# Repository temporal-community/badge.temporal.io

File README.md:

# Temporal Replay 2026 Badge

Public source for the Temporal Replay 2026 Badge at `badge.temporal.io`:
firmware, hardware design files, flashing tools, badge apps, release metadata,
and the static documentation site.

This repository is for people who want to flash a badge, build a badge app,
study or modify the firmware, review the hardware package, or contribute fixes
back through GitHub pull requests. Backend services and private event operations
tooling are intentionally not part of this public repo.

## Choose Your Path

| I want to... | Start here |
|---|---|
| Use or reflash a badge | [Get Started](https://badge.temporal.io/get-started), then [`ignition/README.md`](ignition/README.md) |
| Write a MicroPython badge app | [Developer Guide](https://badge.temporal.io/developer-guide), [Apps](https://badge.temporal.io/apps), and [`firmware/initial_filesystem/apps/README.md`](firmware/initial_filesystem/apps/README.md) |
| Change firmware | [`firmware/README.md`](firmware/README.md) and [`firmware/src/README.md`](firmware/src/README.md) |
| Understand flashing and storage | [`ignition/README.md`](ignition/README.md) and [`firmware/docs/STORAGE-MODEL.md`](firmware/docs/STORAGE-MODEL.md) |
| Work with hardware files | [`hardware/README.md`](hardware/README.md) |
| Update public schedule, floor, or speaker data | [`data/README.md`](data/README.md) |
| Update Community Apps metadata | [`registry/README.md`](registry/README.md) |
| Contribute a fix | Open a pull request against `temporal-community/badge.temporal.io`; see [Contributing](#contributing) below. |

## Repository Map

| Path | What It Contains | Start Here |
|---|---|---|
| [`docs/`](docs/) | Static public documentation site for badge users and contributors. | Visit [badge.temporal.io](https://badge.temporal.io/) or open [`docs/index.html`](docs/index.html) locally. |
| [`firmware/`](firmware/) | PlatformIO firmware project for the ESP32-S3 badge, including native C++ screens, MicroPython embedding, OTA, Doom, and the badge filesystem source. | [`firmware/README.md`](firmware/README.md) |
| [`registry/community_apps/`](registry/community_apps/) | Installable MicroPython community app folders that are published in the Community Apps registry but not preloaded into the factory filesystem. | [`registry/README.md`](registry/README.md) |
| [`ignition/`](ignition/) | Temporal-powered build and flashing system built to bulk flash the badge fleet, also useful for one badge. | [`ignition/README.md`](ignition/README.md) |
| [`hardware/`](hardware/) | Public KiCad projects, fabrication outputs, mechanical references, artwork, and board renders from the final hardware package. | [`hardware/README.md`](hardware/README.md) |
| [`data/`](data/) | Public schedule, speaker, and floor data plus the generated bundle embedded by firmware. | [`data/README.md`](data/README.md) |
| [`registry/`](registry/) | Community Apps registry JSON fetched by badges over WiFi. | [`registry/README.md`](registry/README.md) |
| [`release-assets/`](release-assets/) | Notes for OTA and factory image release artifacts. | [`release-assets/README.md`](release-assets/README.md) |
| [`licenses/`](licenses/) | Third-party license texts and notices for bundled non-MIT components. | [`THIRD_PARTY_NOTICES.md`](THIRD_PARTY_NOTICES.md) |
| [`.github/workflows/`](.github/workflows/) | CI release workflow that builds `firmware.bin` and `replay2026-factory-16MB.bin`. | [`.github/workflows/release-firmware.yml`](.github/workflows/release-firmware.yml) |
| [`CONTRIBUTING.md`](CONTRIBUTING.md) | Pull request guidance and change-type checks. | [`CONTRIBUTING.md`](CONTRIBUTING.md) |

## Quick Start

Ignition is the Temporal-powered system we built to bulk flash the Replay 2026
badge fleet. It runs locally and is the default flashing path for one badge or
a connected batch of badges:

```bash
cd ignition
./setup.sh
./doctor.sh
./start.sh -e replay2026 --firmware-dir ../firmware
```

To preload WiFi during an Ignition build, pass credentials on the command line
or create an ignored `firmware/wifi.local.env` from
[`firmware/wifi.local.env.example`](firmware/wifi.local.env.example):

```bash
./start.sh -e replay2026 --firmware-dir ../firmware \
  --wifi-ssid "YourNetwork" --wifi-pass "YourPassword"
```

Developers who want the lower-level path can use PlatformIO directly:

```bash
cd firmware
pio run -e replay2026
pio run -e replay2026 -t upload
pio run -e replay2026 -t uploadfs
```

For a prebuilt release, download `replay2026-factory-16MB.bin` from
[GitHub Releases](https://github.com/temporal-community/badge.temporal.io/releases).
A factory flash restores firmware and filesystem contents and wipes existing
on-badge data; see [`release-assets/README.md`](release-assets/README.md) for
release artifact context. Flash downloaded factory images with Ignition:

```bash
cd ignition
./start.sh --no-build --factory-image ~/Downloads/replay2026-factory-16MB.bin
```

## Firmware Releases

Public releases include two firmware artifacts:

- `firmware.bin`: application image consumed by badge OTA.
- `replay2026-factory-16MB.bin`: complete factory image with bootloader,
  partition table, firmware, FAT filesystem, and bundled shareware Doom data.

The badge OTA updater checks GitHub Releases in
`temporal-community/badge.temporal.io` for `firmware.bin`.

## Licensing

Temporal-authored source, docs, firmware glue, website content, and hardware
files use the MIT License unless a file or notice says otherwise.

Firmware builds that include Doom also include DoomGeneric engine code and the
bundled `doom1.wad` shareware game data. Those components have separate terms;
see [`THIRD_PARTY_NOTICES.md`](THIRD_PARTY_NOTICES.md) and [`licenses/`](licenses/).

## Generated Artifacts

Some generated files are committed because the firmware or public release flow
consumes them directly:

| Path | Source of truth | Commit? |
|---|---|---|
| `data/out/bundle.bin` and `data/out/*.json` | `data/in/` via `data/build-data.py` | Yes |
| `firmware/data/` | `firmware/initial_filesystem/` via `firmware/scripts/generate_startup_files.py` | No, it is a local build mirror |
| `registry/community_apps.json` | `registry/community_apps/` plus curated registry assets via `firmware/scripts/generate_startup_files.py` | Yes |
| `firmware/.pio/`, `ignition/.venv/`, local logs, and WiFi files | Local machine state | No |
| `firmware.bin` and `replay2026-factory-16MB.bin` | GitHub release workflow | Release assets only |

## Contributing

Pull requests are welcome. Good public contributions include docs fixes,
MicroPython examples, badge apps, firmware fixes, Ignition improvements,
hardware documentation corrections, data updates, and registry updates.
See [`CONTRIBUTING.md`](CONTRIBUTING.md) for change-type checklists.

Before opening a PR:

- Keep changes focused and explain what you tested.
- Link related docs when you add or change a workflow.
- Do not commit credentials, local WiFi settings, virtualenvs, PlatformIO build
  output, caches, or private event operations context.
- For firmware changes, include the relevant PlatformIO build or flash command
  you ran.
- For docs-only changes, check that links resolve from the repo root and the
  static docs site still opens from `docs/index.html`.

Use GitHub issues or PR discussion for questions, bug reports, and proposed
app or documentation changes.

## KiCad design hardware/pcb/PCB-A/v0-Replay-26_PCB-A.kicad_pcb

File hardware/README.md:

# Replay 2026 Badge Hardware

This directory contains the public hardware design package for the Replay 2026
Badge. It includes KiCad source projects, manufacturing outputs, mechanical
reference files, and exported artwork/renders for the two-board badge assembly.

This package is based on the final released hardware files from 2026-05-14.
Editor state, macOS metadata, KiCad lock files, local history folders, embedded
`.git` folders, and generated caches were intentionally left out.

## Directory Map

```text
hardware/
|-- pcb/
|   |-- PCB-A/            # Main badge KiCad project
|   |-- PCB-B/            # Backplate KiCad project
|   `-- assets/           # Board outlines, dimensional DXF/SVG, support STEP
|-- fab/
|   |-- PCB-A/            # Main-board fabrication and assembly outputs
|   `-- PCB-B/            # Backplate fabrication outputs
|-- cad/                  # Thumbstick mechanical STEP references
`-- assets/               # Badge artwork, renders, and exported board views
```

## Board Projects

`pcb/PCB-A/` is the main electronics board. Open
`pcb/PCB-A/v0-Replay-26_PCB-A.kicad_pro` in KiCad to inspect or modify the
main badge PCB.

Important files:

- `v0-Replay-26_PCB-A.kicad_sch`: schematic.
- `v0-Replay-26_PCB-A.kicad_pcb`: PCB layout.
- `Temporal.kicad_sym`: project symbol library.
- `Temporal.pretty/`: project footprint library.
- `fp-lib-table` and `sym-lib-table`: KiCad library table entries.

`pcb/PCB-B/` is the backplate/art board. Open
`pcb/PCB-B/pcb-backplate.kicad_pro` in KiCad to inspect or modify it.

Important files:

- `pcb-backplate.kicad_sch`: schematic.
- `pcb-backplate.kicad_pcb`: PCB layout.
- `pcb-backplate.step`: exported mechanical model.

## Fabrication Outputs

The `fab/` directory contains production-facing outputs. Review these files
before ordering boards, especially if the KiCad source has changed.

### PCB-A: Main Board

`fab/PCB-A/` includes:

- [`fab/PCB-A/V0-Replay-26_PCB-A_GBR_260331-R3.zip`](fab/PCB-A/V0-Replay-26_PCB-A_GBR_260331-R3.zip): main-board Gerber package.
- [`fab/PCB-A/V0-Replay-26_PCB-A_BOM-260331-R1.csv`](fab/PCB-A/V0-Replay-26_PCB-A_BOM-260331-R1.csv): bill of materials.
- [`fab/PCB-A/V0-Replay-26_PCB-A_CPL-260331-R1.csv`](fab/PCB-A/V0-Replay-26_PCB-A_CPL-260331-R1.csv): component placement list.
- [`fab/PCB-A/JLCPCB/V0-Replay-26_PCB-A_BOM-260331-R2.csv`](fab/PCB-A/JLCPCB/V0-Replay-26_PCB-A_BOM-260331-R2.csv): JLCPCB-oriented BOM.
- [`fab/PCB-A/JLCPCB/V0-Replay-26_PCB-A_CPL-260331-R2.csv`](fab/PCB-A/JLCPCB/V0-Replay-26_PCB-A_CPL-260331-R2.csv): JLCPCB-oriented placement.
- [`fab/PCB-A/Elecrow_PCBA_Quote_Temporal-PCB-A_260331-R0.xlsx`](fab/PCB-A/Elecrow_PCBA_Quote_Temporal-PCB-A_260331-R0.xlsx): reviewed public-safe supplier quote context.

The imported production note records the `GBR-R2` change as an increased via
diameter to 0.3 mm plus silkscreen for the SSD1309 display. The included main
Gerber package is `R3`.

### PCB-B: Backplate

`fab/PCB-B/` includes:

- [`fab/PCB-B/v0-Replay-26_PCB-B_GBR-R0.zip`](fab/PCB-B/v0-Replay-26_PCB-B_GBR-R0.zip): backplate Gerber package.
- [`fab/PCB-B/v0-Replay-26_PCB-B_BOM-R0.csv`](fab/PCB-B/v0-Replay-26_PCB-B_BOM-R0.csv): optional assembly BOM.
- [`fab/PCB-B/v0-Replay-26_PCB-B_CPL-R0.csv`](fab/PCB-B/v0-Replay-26_PCB-B_CPL-R0.csv): optional assembly placement list.

See [`fab/PCB-B/README.md`](fab/PCB-B/README.md) for the backplate fabrication
notes. Public production notes:

- 1.6 mm, 2-layer PCB.
- Matte black solder mask with ENIG finish.
- No sample approval required by the original production note.
- No QA/QC or prep required by the original production note.
- BOM/CPL files were provided only for the case where the backplate is SMT
  assembled with Wurth M2 standoffs. The original plan was to skip that SMT
  assembly step.
- Boards can be depanelized if it saves production time.

## Mechanical And Artwork Assets

`cad/` contains thumbstick STEP references:

- `Temporal-Thumbstick-v3.step`
- `Temporal-Thumbstick-v4.step`
- `Temporal-Thumbstick-v5.step`

`pcb/assets/` contains dimensional drawings and support models, including board
outline DXFs, the CR80 reference outline, LED/display STEP references, and a
FreeCAD source file for the badge dimensions. Some optional per-component 3D
model paths in the PCB-A KiCad project point at placeholders under
`pcb/assets/models/`; the original external library models were not included in
the public release package.

`assets/` contains artwork, renders, SVG layer exports, and board-view images
that are useful for documentation and production review. These are source assets
for the public package; they are not required to build firmware.

Useful previews:

- [`assets/export/v0-Replay-26_PCB-A.png`](assets/export/v0-Replay-26_PCB-A.png)
- [`assets/export/v0-Replay-26_PCB-A-Back.png`](assets/export/v0-Replay-26_PCB-A-Back.png)
- [`assets/export/v0-Replay-26_PCB-B.png`](assets/export/v0-Replay-26_PCB-B.png)
- [`assets/graphics/README.md`](assets/graphics/README.md)
- [`pcb/assets/models/README.md`](pcb/assets/models/README.md)

## Naming

Production files use this pattern:

```text
V0-Replay-26_<board>_<filetype>-<date-or-build>-R<revision>.<ext>
```

Examples:

- `V0-Replay-26_PCB-A_GBR_260331-R3.zip`
- `V0-Replay-26_PCB-A_BOM-260331-R1.csv`
- `v0-Replay-26_PCB-B_GBR-R0.zip`

Common file types:

- `GBR`: Gerber fabrication package.
- `BOM`: bill of materials.
- `CPL`: component placement list.

Keep previous released production revisions unless there is a clear reason to
remove them. When generating new production outputs, increment the revision in
the filename and update this README with the relevant change.

## Maintenance Notes

- Keep KiCad source files and manufacturing packages public-safe.
- Do not commit `.DS_Store`, `__MACOSX`, KiCad lock files, `.kicad_prl`,
  `.history` folders, nested `.git` folders, backup files, private supplier
  notes, or generated caches.
- If PCB source files change, regenerate and review the matching Gerber, BOM,
  CPL, and mechanical exports before publishing a release.
- The repository MIT License covers Temporal-authored hardware source unless a
  file or notice says otherwise.

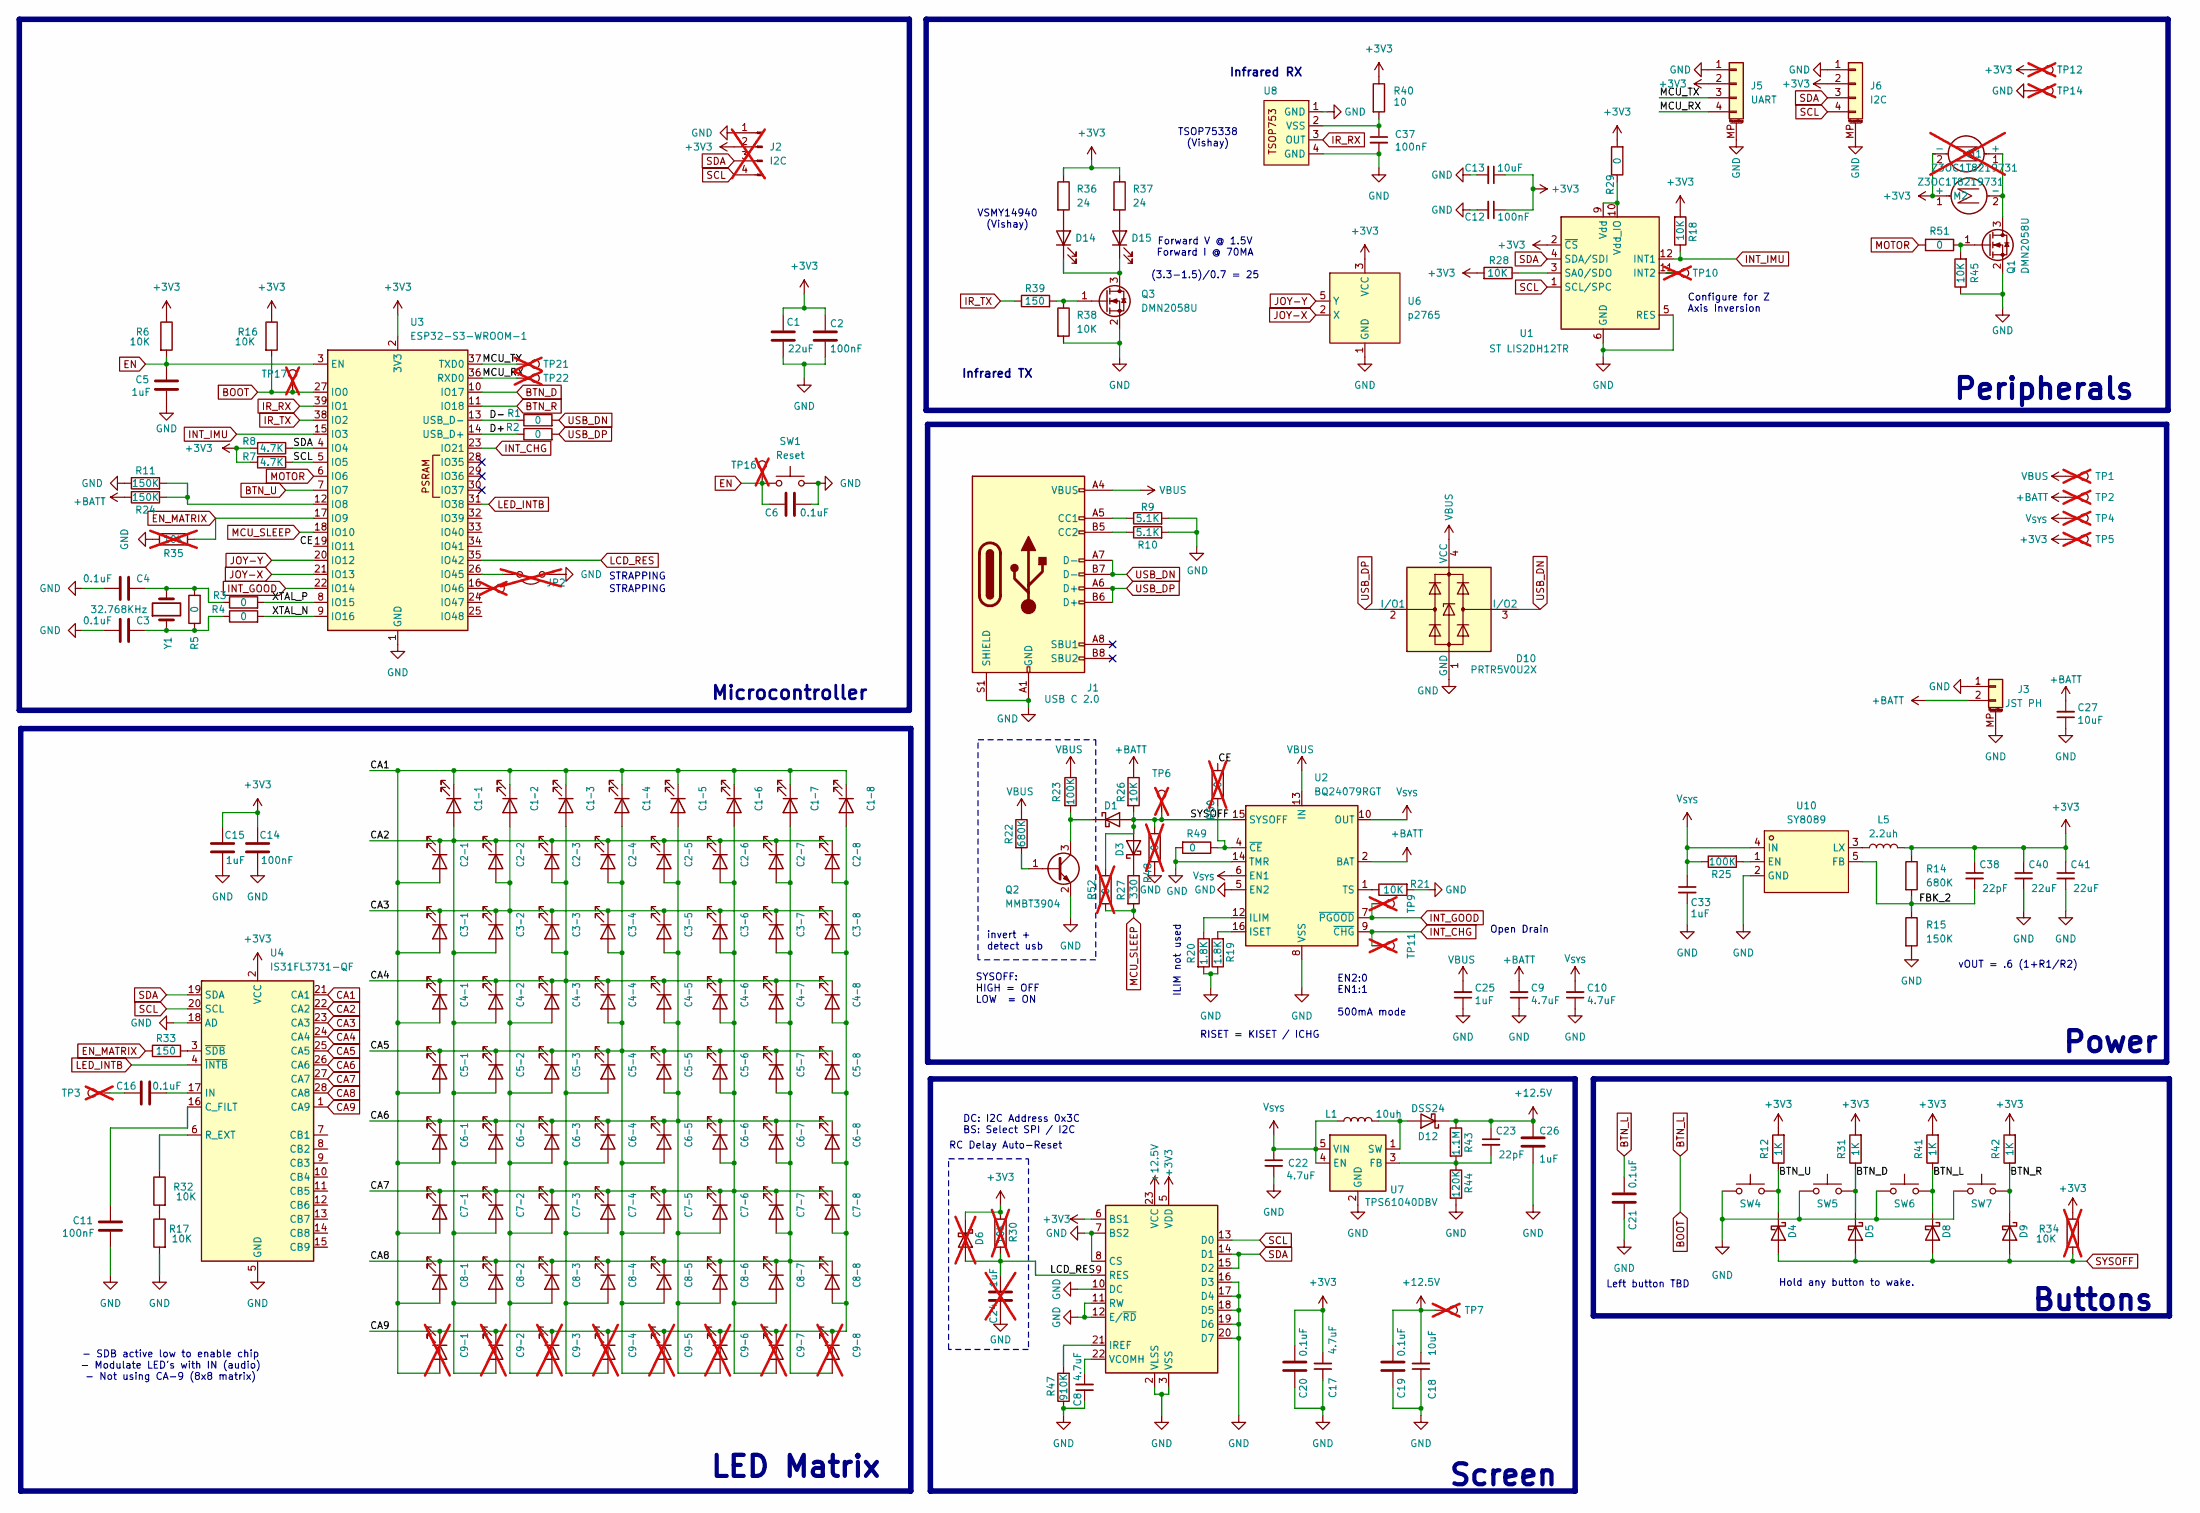
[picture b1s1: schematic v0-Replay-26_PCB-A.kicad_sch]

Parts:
C1, C40, C41: 22uF; C_0402_1005Metric; LCSC C3845593
C1-1, C1-2, C1-3, C1-4, C1-5, C1-6, C1-7, C1-8, C2-1, C2-2, C2-3, C2-4, C2-5, C2-6, C2-7, C2-8, C3-1, C3-2, C3-3, C3-4, C3-5, C3-6, C3-7, C3-8, C4-1, C4-2, C4-3, C4-4, C4-5, C4-6, C4-7, C4-8, C5-1, C5-2, C5-3, C5-4, C5-5, C5-6, C5-7, C5-8, C6-1, C6-2, C6-3, C6-4, C6-5, C6-6, C6-7, C6-8, C7-1, C7-2, C7-3, C7-4, C7-5, C7-6, C7-7, C7-8, C8-1, C8-2, C8-3, C8-4, C8-5, C8-6, C8-7, C8-8: LED0603_NOOUTLINE; CHIPLED_0603_NOOUTLINE; LCSC C19171390
C2, C11, C12, C14, C37: 100nF; C_0402_1005Metric; LCSC C1525
C3, C4, C6, C16, C19, C20, C21: 0.1uF; C_0402_1005Metric; LCSC C1525
C5, C15, C25, C26: 1uF; C_0402_1005Metric; LCSC C14445
C8, C9, C10, C17: 4.7uF; C_0402_1005Metric; LCSC C315248
C9-1, C9-2, C9-3, C9-4, C9-5, C9-6, C9-7, C9-8: LED0603_NOOUTLINE; CHIPLED_0603_NOOUTLINE; not fitted
C13, C18, C27: 10uF; C_0402_1005Metric; LCSC C315248
C22: 4.7uF; C_0402_1005Metric; LCSC C3845593
C23, C38: 22pF; C_0402_1005Metric; LCSC C76960
C24: 1uF; C_0402_1005Metric; LCSC C14445; not fitted
C33: 1uF; C_0402_1005Metric; LCSC C3845593
D1, D3, D4, D5, D8, D9: D_Schottky; D_SOD-523; LCSC C917006
D6: D_Schottky; D_SOD-523; LCSC C917006; not fitted
D10: PRTR5V0U2X; SOT-143; LCSC C5180302
D12: DSS24; D_SOD-123F; LCSC C511865
D14, D15: VSMY14940; vsmy14940; LCSC C511069
J1: USB C 2.0; USB_C_Receptacle_Palconn_UTC16-G; LCSC C2765186
J2: I2C; PinSocket_1x04_P2.54mm_Vertical; not fitted
J3: JST PH; JST_PH_S2B-PH-SM4-TB_1x02-1MP_P2.00mm_Horizontal; LCSC C295747
J5: UART
J6: I2C
JP2: Jumper_2_Open; SolderJumper-2_P1.3mm_Open_RoundedPad1.0x1.5mm; not fitted
L1: 10uh; L_APV_APH0530; LCSC C181721
L5: 2.2uh; L_Coilcraft_LPS3010; LCSC C2926400
M1: Z3OC1T8219731
M2: Z3OC1T8219731; not fitted
Q1, Q3: DMN2058U; SOT-23; LCSC C461001
Q2: MMBT3904; SOT-23; LCSC C916374
R1, R2, R3, R4, R5, R29: 0; R_0201_0603Metric; LCSC C106228
R6, R16, R17, R18, R21, R28, R32, R38, R45: 10K; R_0402_1005Metric; LCSC C60490
R7, R8: 4.7K; R_0402_1005Metric; LCSC C105871
R9, R10: 5.1K; R_0402_1005Metric; LCSC C25905
R11, R15, R24: 150K; R_0402_1005Metric; LCSC C93947
R12, R31, R41, R42: 1K; R_0402_1005Metric; LCSC C106235
R14, R22: 680K; R_0402_1005Metric; LCSC C163456
R19, R20: 1.8K; R_0402_1005Metric; LCSC C203083
R23, R25: 100K; R_0402_1005Metric; LCSC C60491
R26: 10K; R_0402_1005Metric; LCSC C25767
R27: 330; R_0402_1005Metric; LCSC C112291
R30, R34, R35: 10K; R_0402_1005Metric; LCSC C60490; not fitted
R33, R39: 150; R_0402_1005Metric; LCSC C138054
R36, R37: 24; R_0805_2012Metric; LCSC C270625
R40: 10; R_0402_1005Metric; LCSC C138066
R43: 1.1M; R_0402_1005Metric; LCSC C137952
R44: 120K; R_0402_1005Metric; LCSC C114763
R47: 910K; R_0402_1005Metric; LCSC C3921007
R48, R50, R52: 0; R_0402_1005Metric; LCSC C106228; not fitted
R49, R51: 0; R_0402_1005Metric; LCSC C106228
SW1: Reset; SW_SPST_B3U-1000P-B; LCSC C231329
SW4, SW5, SW6, SW7: SW_Push; SW_Push_1TS009xxxx-xxxx-xxxx_6x6x5mm; LCSC C25168849
TP1, TP2, TP3, TP4, TP5, TP6, TP7, TP8, TP9, TP10, TP11, TP12, TP14, TP16, TP17, TP21, TP22: TestPoint; TestPoint_Pad_D1.0mm; not fitted
U1: ST LIS2DH12TR; LGA-12_2x2mm_P0.5mm; LCSC C110926
U2: BQ24079RGT; VQFN-16-1EP_3x3mm_P0.5mm_EP1.6x1.6mm; LCSC C2876751
U3: ESP32-S3-WROOM-1; LCSC C2913202
U4: IS31FL3731-QF; QFN-28-1EP_4x4mm_P0.4mm_EP2.3x2.3mm; LCSC C191206
U5: 24P FPC 0.5MM; TE_2-1734839-4_1x24-1MP_P0.5mm_Horizontal
U6: p2765; JOYSTICK_ANALOG_MINITHM
U7: TPS61040DBV; SOT-23-5; LCSC C9846
U8: TSOP75338; TSOP753; LCSC C499550
U10: SY8089; SOT-23-5; LCSC Part C79313
Y1: 32.768KHz; Crystal_SMD_3215-2Pin_3.2x1.5mm; LCSC C97606

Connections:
+3V3: C1.1, C2.1, C12.1, C13.1, C14.1, C15.1, C17.2, C20.2, C38.1, C40.1, C41.1, D6.1 (K), J2.2, J5.2, J6.2, L5.2, M1.1 (+), M2.2 (-), R6.1, R7.2, R8.2, R12.2, R14.1, R16.1, R18.2, R28.2, R29.2, R30.1, R31.2, R34.1, R36.1, R37.1, R40.1, R41.2, R42.2, TP5.1, TP12.1, U1.2 (~CS), U3.2 (3V3), U4.2 (VCC), U5.5 (VDD), U5.6 (BS1), U6.3 (VCC), U6.4 (VCC)
+12.5V: C18.2, C19.2, C23.1, C26.2, D12.1 (K), R43.1, TP7.1, U5.23 (VCC)
+BATT: C9.2, C27.2, J3.2, R24.1, R26.1, TP2.1, U2.2 (BAT), U2.3 (BAT)
/CE: R50.2, U3.19 (IO11)
/D+: R2.1, U3.14 (USB_D+)
/D-: R1.1, U3.13 (USB_D-)
/FBK_2: C38.2, R14.2, R15.1, U10.5 (FB)
/MCU_RX: J5.4, TP22.1, U3.36 (RXD0)
/MCU_TX: J5.3, TP21.1, U3.37 (TXD0)
/XTAL_N: R4.2, U3.9 (IO16)
/XTAL_P: R3.2, U3.8 (IO15)
BOOT: C21.2, D8.1 (K), R16.2, R41.1, SW6.2, TP17.1, U3.27 (IO0)
BTN_D: D5.1 (K), R31.1, SW5.2, U3.10 (IO17)
BTN_R: D9.1 (K), R42.1, SW7.2, U3.11 (IO18)
BTN_U: D4.1 (K), R12.1, SW4.2, U3.7 (IO7)
CA1: C1-1.1 (K), C1-2.1 (K), C1-3.1 (K), C1-4.1 (K), C1-5.1 (K), C1-6.1 (K), C1-7.1 (K), C1-8.1 (K), C2-1.2 (A), C3-1.2 (A), C4-1.2 (A), C5-1.2 (A), C6-1.2 (A), C7-1.2 (A), C8-1.2 (A), C9-1.2 (A), U4.21 (CA1)
CA2: C1-1.2 (A), C2-1.1 (K), C2-2.1 (K), C2-3.1 (K), C2-4.1 (K), C2-5.1 (K), C2-6.1 (K), C2-7.1 (K), C2-8.1 (K), C3-2.2 (A), C4-2.2 (A), C5-2.2 (A), C6-2.2 (A), C7-2.2 (A), C8-2.2 (A), C9-2.2 (A), U4.22 (CA2)
CA3: C1-2.2 (A), C2-2.2 (A), C3-1.1 (K), C3-2.1 (K), C3-3.1 (K), C3-4.1 (K), C3-5.1 (K), C3-6.1 (K), C3-7.1 (K), C3-8.1 (K), C4-3.2 (A), C5-3.2 (A), C6-3.2 (A), C7-3.2 (A), C8-3.2 (A), C9-3.2 (A), U4.23 (CA3)
CA4: C1-3.2 (A), C2-3.2 (A), C3-3.2 (A), C4-1.1 (K), C4-2.1 (K), C4-3.1 (K), C4-4.1 (K), C4-5.1 (K), C4-6.1 (K), C4-7.1 (K), C4-8.1 (K), C5-4.2 (A), C6-4.2 (A), C7-4.2 (A), C8-4.2 (A), C9-4.2 (A), U4.24 (CA4)
CA5: C1-4.2 (A), C2-4.2 (A), C3-4.2 (A), C4-4.2 (A), C5-1.1 (K), C5-2.1 (K), C5-3.1 (K), C5-4.1 (K), C5-5.1 (K), C5-6.1 (K), C5-7.1 (K), C5-8.1 (K), C6-5.2 (A), C7-5.2 (A), C8-5.2 (A), C9-5.2 (A), U4.25 (CA5)
CA6: C1-5.2 (A), C2-5.2 (A), C3-5.2 (A), C4-5.2 (A), C5-5.2 (A), C6-1.1 (K), C6-2.1 (K), C6-3.1 (K), C6-4.1 (K), C6-5.1 (K), C6-6.1 (K), C6-7.1 (K), C6-8.1 (K), C7-6.2 (A), C8-6.2 (A), C9-6.2 (A), U4.26 (CA6)
CA7: C1-6.2 (A), C2-6.2 (A), C3-6.2 (A), C4-6.2 (A), C5-6.2 (A), C6-6.2 (A), C7-1.1 (K), C7-2.1 (K), C7-3.1 (K), C7-4.1 (K), C7-5.1 (K), C7-6.1 (K), C7-7.1 (K), C7-8.1 (K), C8-7.2 (A), C9-7.2 (A), U4.27 (CA7)
CA8: C1-7.2 (A), C2-7.2 (A), C3-7.2 (A), C4-7.2 (A), C5-7.2 (A), C6-7.2 (A), C7-7.2 (A), C8-1.1 (K), C8-2.1 (K), C8-3.1 (K), C8-4.1 (K), C8-5.1 (K), C8-6.1 (K), C8-7.1 (K), C8-8.1 (K), C9-8.2 (A), U4.28 (CA8)
CA9: C1-8.2 (A), C2-8.2 (A), C3-8.2 (A), C4-8.2 (A), C5-8.2 (A), C6-8.2 (A), C7-8.2 (A), C8-8.2 (A), C9-1.1 (K), C9-2.1 (K), C9-3.1 (K), C9-4.1 (K), C9-5.1 (K), C9-6.1 (K), C9-7.1 (K), C9-8.1 (K), U4.1 (CA9)
EN: C5.1, C6.1, R6.2, SW1.2, TP16.1, U3.3 (EN)
EN_MATRIX: R33.1, R35.2, U3.17 (IO9)
GND: C1.2, C2.2, C3.2, C4.2, C5.2, C6.2, C8.1, C9.1, C10.1, C11.2, C12.2, C13.2, C14.2, C15.2, C17.1, C18.1, C19.1, C20.1, C21.1, C22.2, C24.2, C25.1, C26.1, C27.1, C33.2, C37.2, C40.2, C41.2, D10.1 (GND), J1.A1 (GND), J1.A12 (GND), J1.B1 (GND), J1.B12 (GND), J1.S1 (SHIELD), J2.1, J3.1, J3.MP (MountPin), J5.1, J5.MP (MountPin), J6.1, J6.MP (MountPin), JP2.2 (B), Q1.2 (S), Q2.2 (E), Q3.2 (S), R9.2, R10.2, R11.1, R15.2, R17.2, R19.1, R20.2, R21.2, R35.1, R38.2, R44.2, R45.1, R47.1, R48.1, R49.2, SW1.1, SW4.1, SW5.1, SW6.1, SW7.1, TP14.1, U1.5 (RES), U1.6 (GND), U1.7 (GND), U1.8 (GND), U2.5 (EN2), U2.8 (VSS), U2.14 (TMR), U2.17 (VSS), U3.1 (GND), U3.40 (GND), U3.41 (GND), U4.5 (GND), U4.18 (AD), U4.29 (GND), U5.1 (NC), U5.2 (VLSS), U5.3 (VSS), U5.4 (NC), U5.7 (BS2), U5.8 (CS), U5.10 (DC), U5.11 (RW), U5.12 (E/~RD), U5.16 (D3), U5.17 (D4), U5.18 (D5), U5.19 (D6), U5.20 (D7), U5.24 (NC), U5.MP, U6.1 (GND), U6.6 (GND), U7.2 (GND), U8.1 (GND), U8.4 (GND), U10.2 (GND)
INT_CHG: TP11.1, U2.9 (~CHG), U3.23 (IO21)
INT_GOOD: TP9.1, U2.7 (~PGOOD), U3.22 (IO14)
INT_IMU: R18.1, U1.12 (INT1), U3.15 (IO3)
IR_RX: U3.39 (IO1), U8.3 (OUT)
IR_TX: R39.1, U3.38 (IO2)
JOY-X: U3.21 (IO13), U6.2 (X)
JOY-Y: U3.20 (IO12), U6.5 (Y)
LCD_RES: C24.1, D6.2 (A), R30.2, U3.35 (IO42), U5.9 (RES)
LED_INTB: U3.31 (IO38), U4.4 (~INTB)
MCU_SLEEP: R27.2, R52.2, U3.18 (IO10)
MOTOR: R51.2, U3.6 (IO6)
unnamed: C3.1, R4.1, R5.1, Y1.1
unnamed: C4.1, R3.1, R5.2, Y1.2
unnamed: C16.1, TP3.1
unnamed: D1.1 (K), Q2.3 (C), R23.2
unnamed: D3.1 (K), R27.1
unnamed: D12.2 (A), L1.2, U7.1 (SW)
unnamed: D14.2 (A), R36.2
unnamed: D14.1 (K), D15.1 (K), Q3.3 (D)
unnamed: D15.2 (A), R37.2
unnamed: J1.A5 (CC1), R9.1
unnamed: J1.B5 (CC2), R10.1
unnamed: JP2.1 (A), U3.26 (IO45)
unnamed: M1.2 (-), M2.1 (+), Q1.3 (D)
unnamed: Q1.1 (G), R45.2, R51.1
unnamed: Q2.1 (B), R22.2
unnamed: Q3.1 (G), R38.1, R39.2
unnamed: R17.1, R32.2
unnamed: TP10.1, U1.11 (INT2)
unnamed: R28.1, U1.3 (SA0/SDO)
unnamed: R29.1, U1.9 (Vdd), U1.10 (Vdd_IO)
unnamed: R20.1, U2.12 (ILIM)
unnamed: R19.2, U2.16 (ISET)
unnamed: R21.1, U2.1 (TS)
unnamed: R49.1, R50.1, U2.4 (~CE)
unnamed: R11.2, R24.2, U3.12 (IO8)
unnamed: TP8.1, U3.16 (IO46)
unnamed: C11.1, U4.16 (C_FILT)
unnamed: C16.2, U4.17 (IN)
unnamed: R32.1, U4.6 (R_EXT)
unnamed: R33.2, U4.3 (~SDB)
unnamed: R47.2, U5.21 (IREF)
unnamed: C8.2, U5.22 (VCOMH)
unnamed: C23.2, R43.2, R44.1, U7.3 (FB)
unnamed: C37.1, R40.2, U8.2 (VSS)
unnamed: R25.2, U10.1 (EN)
unnamed: L5.1, U10.3 (LX)
SCL: J2.4, J6.4, R7.1, U1.1 (SCL/SPC), U3.5 (IO5), U4.20 (SCL), U5.13 (D0)
SDA: J2.3, J6.3, R8.1, U1.4 (SDA/SDI), U3.4 (IO4), U4.19 (SDA), U5.14 (D1), U5.15 (D2)
SYSOFF: D1.2 (A), D3.2 (A), D4.2 (A), D5.2 (A), D8.2 (A), D9.2 (A), R26.2, R34.2, R48.2, R52.1, TP6.1, U2.15 (SYSOFF)
USB_DN: D10.3 (I/O2), J1.A7 (D-), J1.B7 (D-), R1.2
USB_DP: D10.2 (I/O1), J1.A6 (D+), J1.B6 (D+), R2.2
VBUS: C25.2, D10.4 (VCC), J1.A4 (VBUS), J1.A9 (VBUS), J1.B4 (VBUS), J1.B9 (VBUS), R22.1, R23.1, TP1.1, U2.13 (IN)
V_{SYS}: C10.2, C22.1, C33.1, L1.1, R25.1, TP4.1, U2.6 (EN1), U2.10 (OUT), U2.11 (OUT), U7.4 (EN), U7.5 (VIN), U10.4 (IN)

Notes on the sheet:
Power
RISET = KISET / ICHG
SYSOFF: HIGH = OFF LOW = ON
Configure for Z Axis Inversion
EN2:0 EN1:1 500mA mode
DC: I2C Address 0x3C BS: Select SPI / I2C
ILIM not used
Forward V @ 1.5V Forward I @ 70MA (3.3-1.5)/0.7 = 25
LED Matrix
vOUT = .6 (1+R1/R2)
Left button TBD
Microcontroller
RC Delay Auto-Reset
- SDB active low to enable chip - Modulate LED's with IN (audio) - Not using CA-9 (8x8 matrix)
TSOP75338 (Vishay)
Open Drain
STRAPPING
Infrared TX
Peripherals
invert + detect usb
Buttons
VSMY14940 (Vishay)
Infrared RX
Hold any button to wake.
Screen

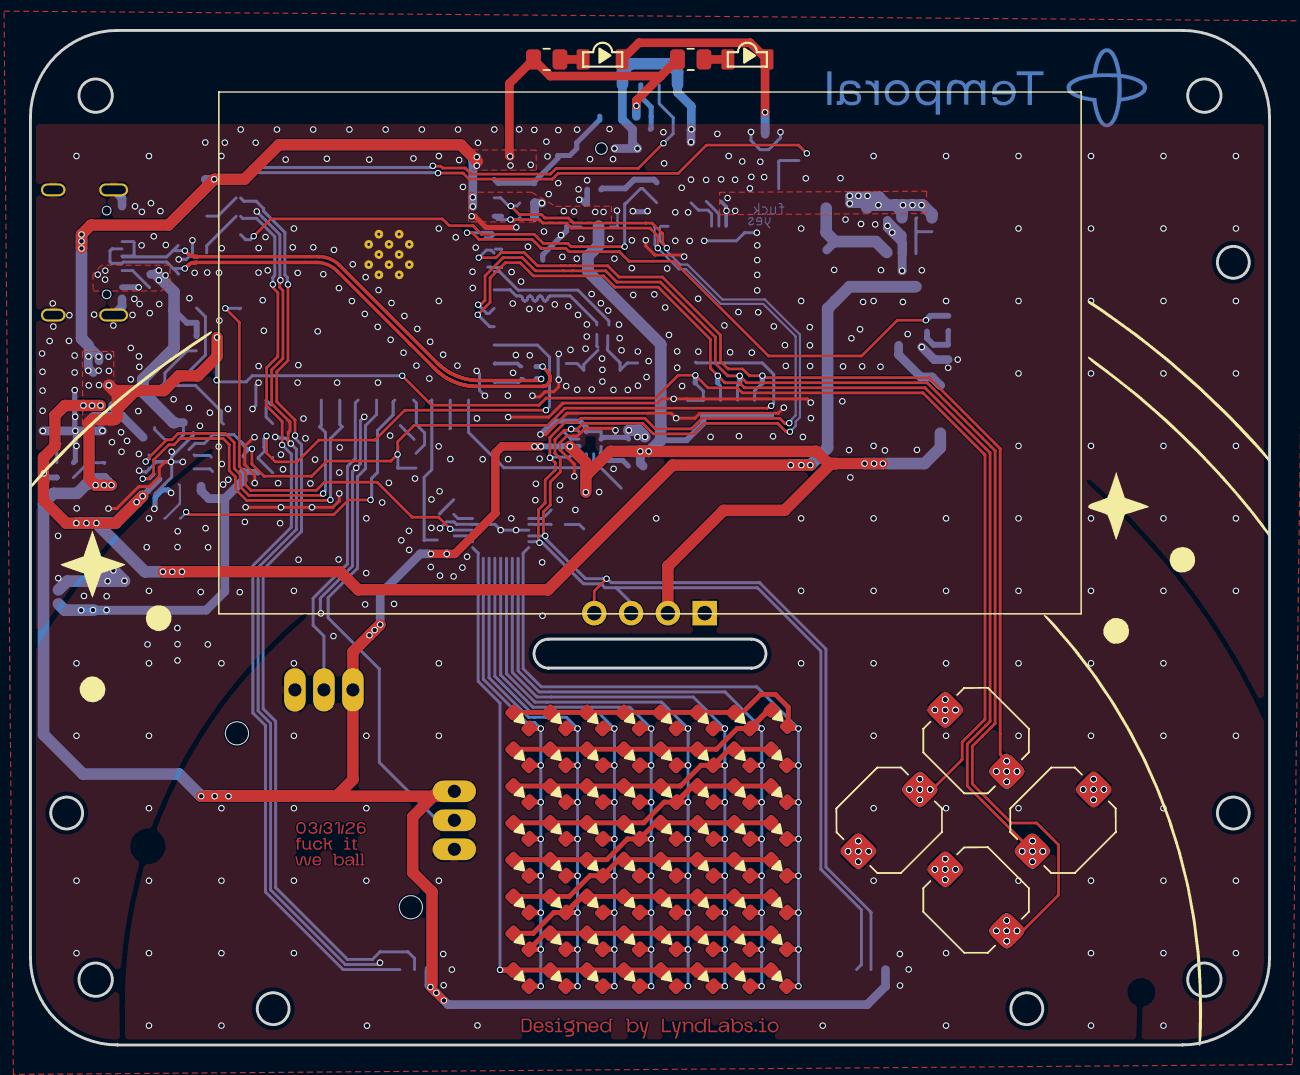
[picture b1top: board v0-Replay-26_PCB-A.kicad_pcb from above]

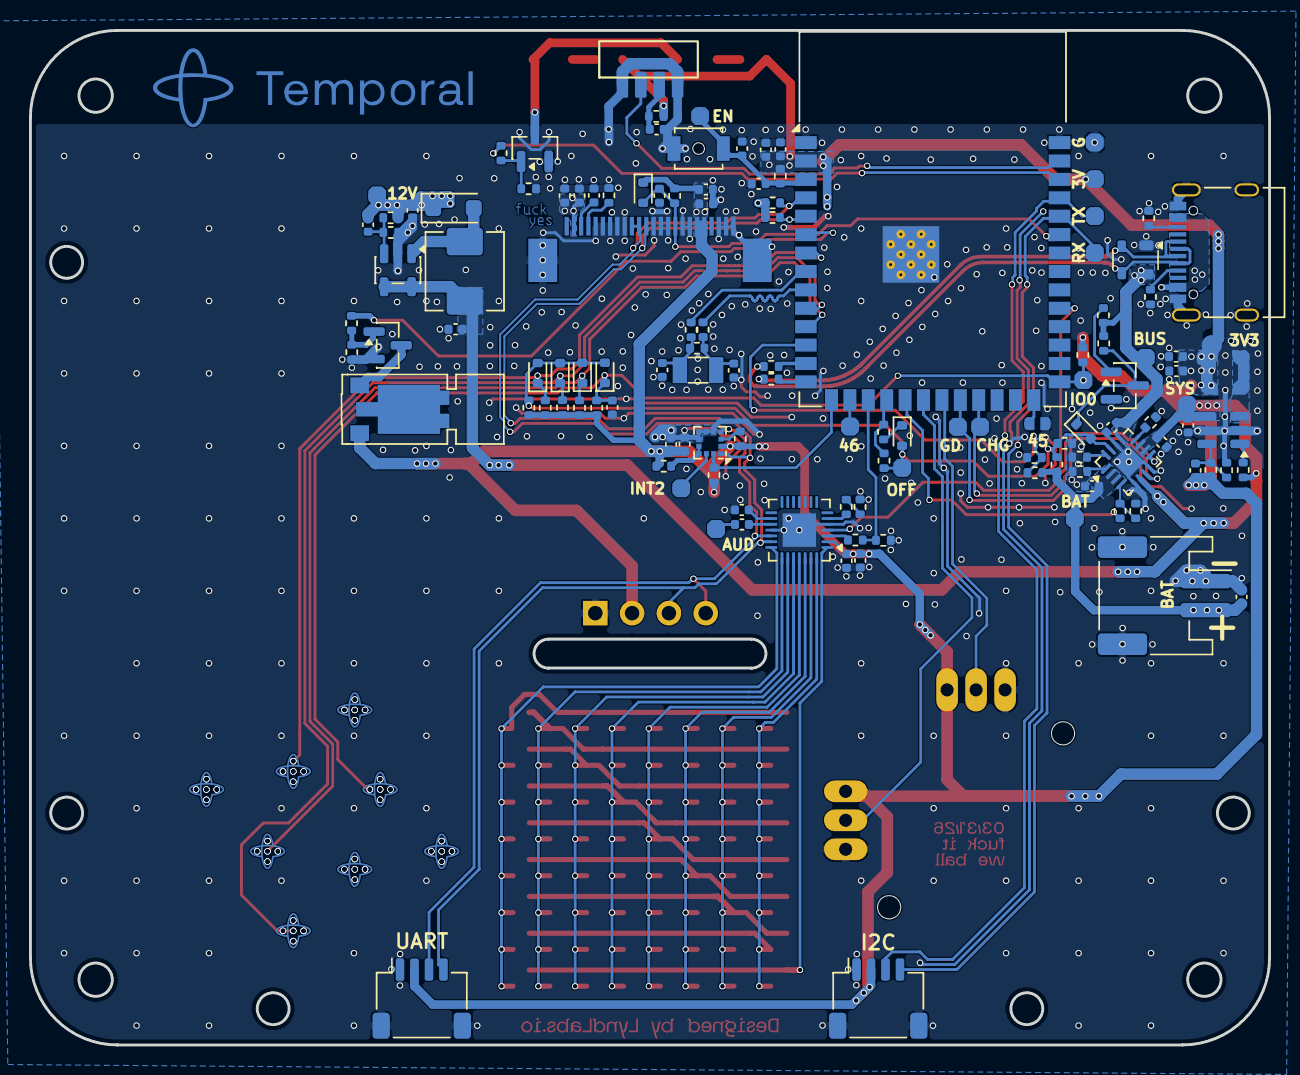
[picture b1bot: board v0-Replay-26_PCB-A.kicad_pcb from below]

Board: 2 copper layers, 85.5 x 70.0 mm, 200 parts (127 on the bottom side), 81 nets.

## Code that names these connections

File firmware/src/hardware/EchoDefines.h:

#ifndef ECHO_DEFINES_H
#define ECHO_DEFINES_H

#define JOY_Y 12
#define JOY_X 13

#define BUTTON_RIGHT 18
#define BUTTON_DOWN  17
#define BUTTON_LEFT  0 //this is marked as X on schematic. You need to move the 0 ohm resistor to the other position.
#define BUTTON_UP    7

#define SDA_PIN 4
#define SCL_PIN 5

#define IR_RX_PIN 1 // TSOP75338
#define IR_TX_PIN 2

#define MCU_SLEEP_PIN 10
#define INT_PWR_PIN 13
#define INT_GP_PIN 3  // For the LIS2DH12TR accelerometer (interrupt / SA0 per schematic) Also SYSOFF for BQ24079
#define ACCEL_INT_PIN 3
#define TILT_PIN 3

#define SYSOFF_PIN 10

#define BATT_VOLTAGE_PIN 8 // VBATT - 150K - BATT_VOLTAGE_PIN - 150K - GND
#define CHG_GOOD_PIN 14
#define CHG_STAT_PIN 21
#define CE_PIN 11

#define NAPTIME_LIGHT_SLEEP_AFTER_NO_MOTION_MS 30000UL
#define NAPTIME_DEEP_SLEEP_AFTER_NO_MOTION_MS 300000UL
#define NAPTIME_LIGHT_SLEEP_POLL_MS 1000UL

#define MOTOR_PIN 6

#define LIS2DH12_I2C_ADDRESS 0x19

#define LED_MATRIX_INTB_PIN 38    //IS31FL3731 LED Matrix driver
#define LED_MATRIX_AUDIO_PIN 38
#define LED_MATRIX_ENABLE_PIN 9

#define LED_MATRIX_WIDTH 8
#define LED_MATRIX_HEIGHT 8
#define LED_MATRIX_I2C_ADDRESS 0x74

#define LCD_RES_PIN 42
#define LCD_INVERTED 0

#define OLED_I2C_ADDRESS 0x3C

#define OLED_WIDTH 128
#define OLED_HEIGHT 64


// ── Per-peripheral feature flags ─────────────────────────────────────────────
// Code includes/excludes hardware drivers based on these flags.
// Add matching flags to any new hardware config file to enable the peripheral.
#define BADGE_HAS_IMU           // LIS2DH12 accelerometer
#define BADGE_HAS_LED_MATRIX    // IS31FL3731 8×8 LED matrix
#define BADGE_HAS_HAPTICS       // Vibration motor
#define BADGE_HAS_BATTERY_GAUGE // ADC voltage divider on BATT_VOLTAGE_PIN
#define BADGE_HAS_SLEEP_SERVICE // Motion-based sleep (requires IMU)

#define BADGE_ECHO


#endif

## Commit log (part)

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2026-04-29 Add favicon, styles
2026-04-29 More style updates
2026-04-29 Make badge more mobile friendly
2026-04-29 More mobile fixes
2026-04-29 Add CODEOWNERS
2026-04-30 Update badge developer guide content
2026-04-30 Restore Temporal header links
2026-04-30 Update titles
2026-05-07 Edit pass; adds 'Basics' page
2026-05-07 Changes to Basics, removed Getting Started
2026-05-07 more tweaks. removed boops
2026-05-15 Add first community badge apps
2026-05-15 Initial public release
2026-05-16 fetch a dad joke from dadjokes736.com
